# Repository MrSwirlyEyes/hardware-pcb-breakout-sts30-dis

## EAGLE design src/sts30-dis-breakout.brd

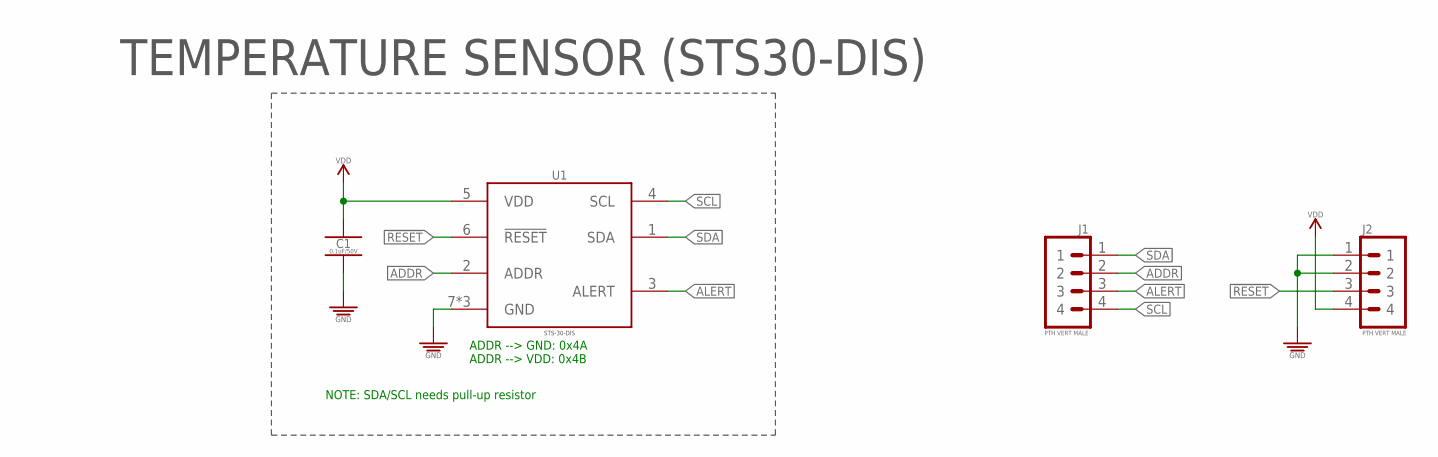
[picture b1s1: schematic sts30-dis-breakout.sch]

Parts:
C1: 0.1uF/50V; CAPC1005X55_SMD-0402
J1, J2: PTH VERT MALE; HDRV4W64P254_1X4_1016X254X838B
U1: STS-30-DIS; SON50P250X250X100-9T110X180N

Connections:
!RESET!: J2.3, U1.6 (!RESET!)
ADDR: J1.2, U1.2 (ADDR)
ALERT: J1.3, U1.3 (ALERT)
GND: C1.2, J2.1, J2.2, U1.7 (GND), U1.8 (GND), U1.9 (GND)
SCL: J1.4, U1.4 (SCL)
SDA: J1.1, U1.1 (SDA)
VDD: C1.1, J2.4, U1.5 (VDD)

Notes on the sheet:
TEMPERATURE SENSOR (STS30-DIS)
NOTE: SDA/SCL needs pull-up resistor
ADDR --> GND: 0x4A ADDR --> VDD: 0x4B

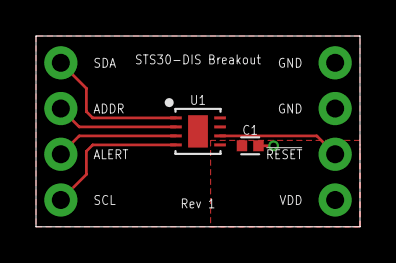
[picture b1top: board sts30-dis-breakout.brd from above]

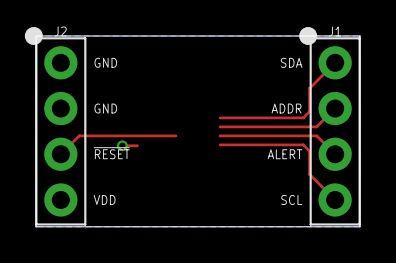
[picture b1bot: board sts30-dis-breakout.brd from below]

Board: 2 copper layers, 18.0 x 10.6 mm, 4 parts (2 on the bottom side), 7 nets.

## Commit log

2021-08-11 Initialize repo.
